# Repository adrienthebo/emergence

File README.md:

# Emergence

> Electronics is magic with well understood rules.
> - Lizzi Lindboe

## Design resources

- [LED Series Resistor Calculator](https://www.digikey.com/en/resources/conversion-calculators/conversion-calculator-led-series-resistor)

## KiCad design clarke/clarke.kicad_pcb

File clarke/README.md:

# Clarke PCB

## History

[Edith Clarke] was the first female electrical engineer and the first female
professor of electrical engineering. Clarke invented the Clarke calculator, a
graphical device for solving equations for electrical voltage, current, and
impedance in power transmission lines.

[Edith Clarke]: https://en.wikipedia.org/wiki/Edith_Clarke

## Compatibility

- Teensy 3.1
- Teensy 3.2

## Design requirements

- [x] Power LED
- [x] Power LED current limiting
- [x] Push buttons
- [x] Connector for SPI expansion board
- [x] Connector for WS2811 expansion board
- [x] Potentiometer
- [ ] Level shifter for OCTO1 (74LV1T125)
- [ ] Current limiting resistor for OCTO1 DO pin
- [x] SPI CS pullup resistor
- [x] Serial interface

## Design ideas

- [ ] ESD protection for SPI?
- [ ] Push button LEDs
- [ ] Current limiting for WS2811 +5V
- [x] Break out I2C pins
- [x] Additional user controllable LEDs on PWM pins

## Constraints

- Teensy LC
  - Pins 3 and 4 are reserved for OctoWS2811
  - All pins must not be connected to +5V; Teensy LC is is not 5V tolerant.

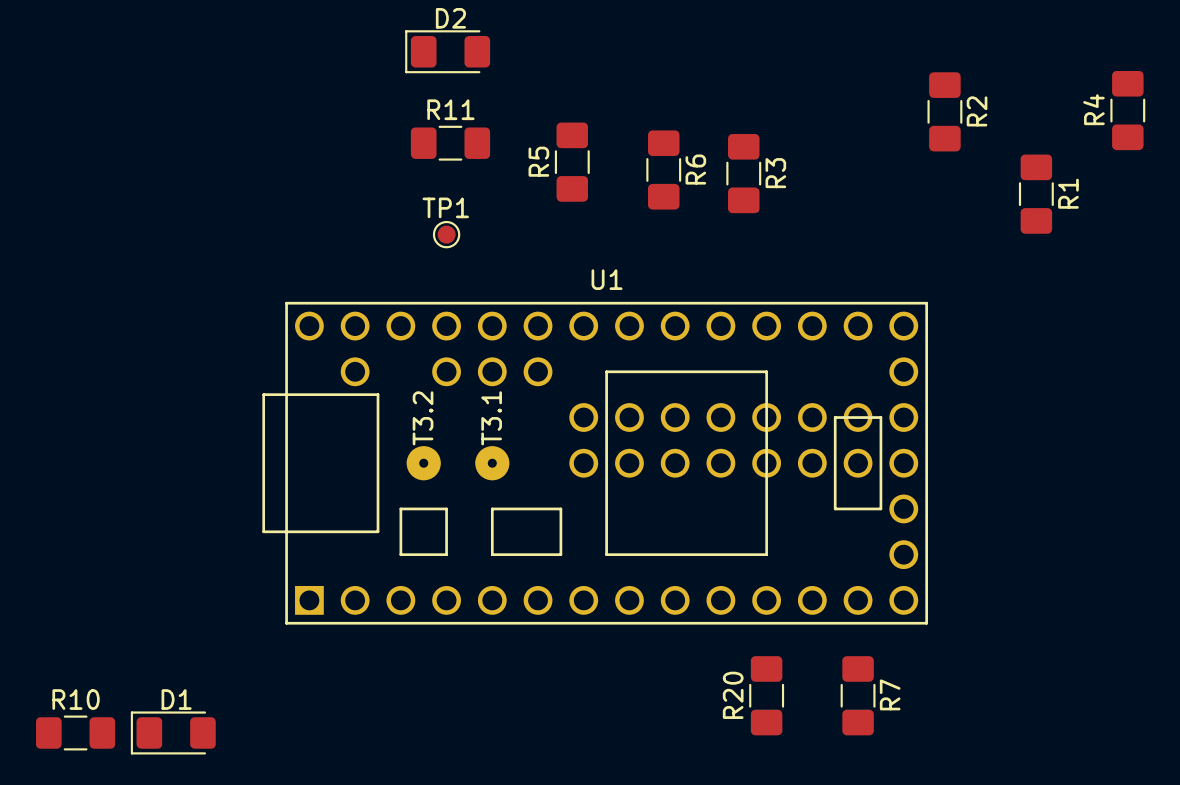
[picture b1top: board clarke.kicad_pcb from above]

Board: 2 copper layers, 14 parts (0 on the bottom side), 14 nets, no tracks yet.

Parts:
D1: BLUE LED; D_1206_3216Metric_Pad1.42x1.75mm_HandSolder
D2: RED LED; D_1206_3216Metric_Pad1.42x1.75mm_HandSolder
R1, R2, R3, R4, R7, R20: 10K; R_1206_3216Metric_Pad1.42x1.75mm_HandSolder
R5, R6: 4K7; R_1206_3216Metric_Pad1.42x1.75mm_HandSolder
R10: 100; R_1206_3216Metric_Pad1.42x1.75mm_HandSolder
R11: 220; R_1206_3216Metric_Pad1.42x1.75mm_HandSolder
TP1: TestPoint; TestPoint_Pad_D1.0mm
U1: Teensy3.2; Teensy30_31_32_LC

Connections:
+3V3: R1.1, R2.1, R3.1, R4.1, R5.1, R6.1, R20.1, U1.31
+5V: R10.1, U1.33
/DE1: R7.1, U1.12
/POT1: R1.2, U1.22
/SCL: R5.2, U1.26
/SDA: R6.2, U1.25
/SW1: R2.2, U1.23
/SW2: R3.2, U1.24
/SW3: R4.2, U1.29
/~CS1: R20.2, U1.11
GND: D1.1, D2.1, R7.2, U1.1
unnamed: D1.2, R10.2
unnamed: D2.2, R11.2
unnamed: R11.1, TP1.1, U1.30

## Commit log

2019-04-09 Add empty clarke schematic
2019-04-09 Add teensy library and footprints
2019-04-10 Add teensy library to schematic library
2019-04-11 clark: add teensy, power
2019-04-11 Ignore trailing whitespace in .sch files
2019-04-11 clark: Remove obsolete octows2811 jumper, add no connects
2019-04-11 clarke: Clean up labels, add SPI connector
2019-04-11 clarke: flesh out design requirements
2019-04-11 clarke: Add preliminary README
2019-04-11 clarke: document power connector
2019-04-11 Add README with witty quote
2019-04-11 clarke: add potentiometer
2019-04-11 clarke: push buttons are implemented
2019-04-11 clarke: add schottky diode for Teensy VIN
2019-04-11 clarke: power LED has been implemented
2019-04-11 clarke: Relocate button/pot symbols
2019-04-11 gitattributes: treat schematics as binary
2019-04-11 clarke: update design requirements
2019-04-12 reference: add Teensy 3.2 pinouts
2019-04-12 clarke: add more design entries
2019-04-12 clarke: Add PWR_FLAG for Teensy VIN pin
    Because VIN can be a power input and power output, depending on the use
    of the USB cable, the ERC will generate an error about the unpowered
    pin. Attaching a power flag solves this issue.
2019-04-12 clarke: Drop schottky diode from Teensy VIN
    The schottky diode has to be soldered onto the Teensy itself if the
    board can be powered from both USB and the power connector; we can't
    solve this on the main PCB.
2019-04-12 clarke: free up I2C pins
2019-04-12 clarke: CS signals are inverted
2019-04-12 README: document LED series resistor calculator
2019-04-12 clarke: design requirement updates
2019-04-12 clarke: add SPI ~CS pullup resistor, update supported boards
    The current design uses pullup resistors connected to +5V; this will
    toast a Teensy LC board since it's not 5v tolerant.
2019-04-12 clarke: add current limiting resistors to SPI connector
2019-04-12 clarke: expose I2C header, mirror power connection
2019-04-12 clarke: remove SPI protection resistors
2019-04-12 reference: add teensy 3.2 schematic
2019-04-12 clarke: Connect pullup resistors to +3V3
2019-04-12 clarke: Add I2C pullup resistors
2019-04-12 clarke: Add extra LED on PWM pin
2019-04-12 clarke: clearly label LED colors
2019-04-12 Add serial interface headers
2019-04-12 clarke: update schematic version to v0.1.0
2019-04-13 clarke: Partially associate footprints
2019-04-13 clarke: update projects with pcbnew configuration
2019-04-13 clarke: add fp-lib-table
2019-04-15 clarke: associate schematic symbols with footprints
2019-04-15 clarke: add preliminary PCB layout
